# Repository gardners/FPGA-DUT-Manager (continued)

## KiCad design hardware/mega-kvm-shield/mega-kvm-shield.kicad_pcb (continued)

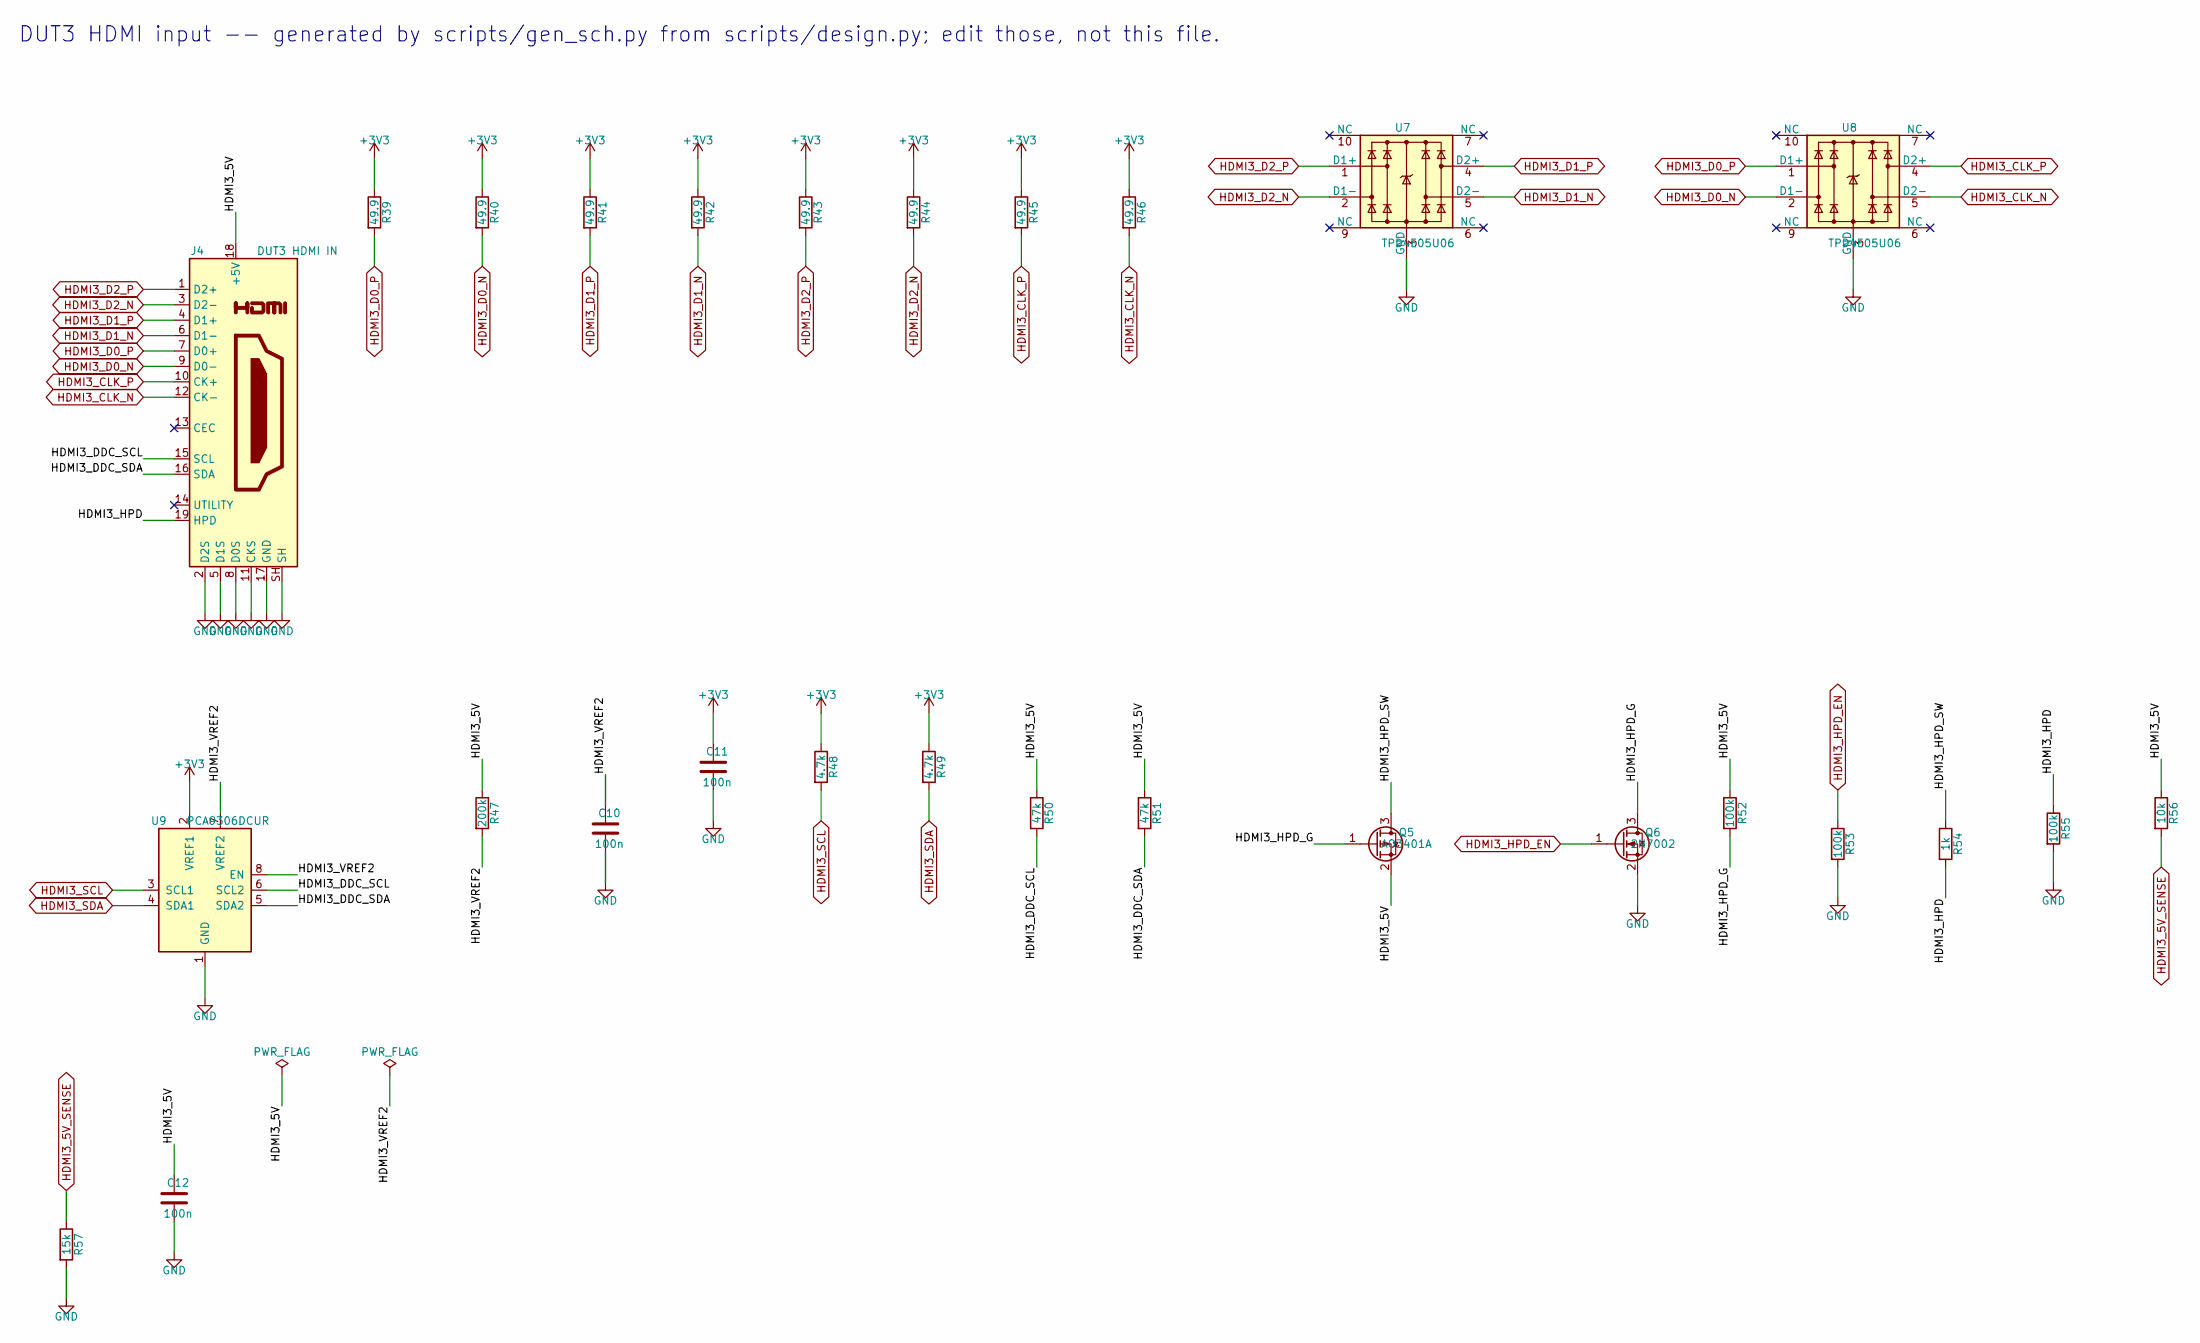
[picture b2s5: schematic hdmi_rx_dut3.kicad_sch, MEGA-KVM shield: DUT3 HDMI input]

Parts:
C10, C11, C12: 100n; C_0402_1005Metric; LCSC C1525
J4: DUT3 HDMI IN; HDMI_A_Amphenol_10029449-x01xLF_Horizontal; MPN Amphenol 10029449-111RLF
Q5: AO3401A; SOT-23; LCSC C15127
Q6: 2N7002; SOT-23; LCSC C8545
R39, R40, R41, R42, R43, R44, R45, R46: 49.9; R_0402_1005Metric; LCSC C25120
R47: 200k; R_0402_1005Metric; LCSC C25811
R48, R49: 4.7k; R_0402_1005Metric; LCSC C25900
R50, R51: 47k; R_0402_1005Metric; LCSC C25792
R52, R53, R55: 100k; R_0402_1005Metric; LCSC C25741
R54: 1k; R_0402_1005Metric; LCSC C11702
R56: 10k; R_0402_1005Metric; LCSC C25744
R57: 15k; R_0402_1005Metric; LCSC C25756
U7, U8: TPD4E05U06; USON-10_2.5x1.0mm_P0.5mm; LCSC C138714
U9: PCA9306DCUR; VSSOP-8_2.3x2mm_P0.5mm

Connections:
+3V3: C11.1, R39.1, R40.1, R41.1, R42.1, R43.1, R44.1, R45.1, R46.1, R48.1, R49.1, U9.2 (VREF1); also elsewhere on the board
GND: C10.2, C11.2, C12.2, J4.2 (D2S), J4.5 (D1S), J4.8 (D0S), J4.11 (CKS), J4.17 (GND), J4.SH, Q6.2 (S), R53.2, R55.2, R57.2, U7.3 (GND), U7.8 (GND), U8.3 (GND), U8.8 (GND), U9.1 (GND); also elsewhere on the board
HDMI3_5V: C12.1, J4.18 (+5V), Q5.2 (S), R47.1, R50.1, R51.1, R52.1, R56.1
HDMI3_5V_SENSE: R56.2, R57.1; also elsewhere on the board
HDMI3_CLK_N: J4.12 (CK-), R46.2, U8.5 (D2-); also elsewhere on the board
HDMI3_CLK_P: J4.10 (CK+), R45.2, U8.4 (D2+); also elsewhere on the board
HDMI3_D0_N: J4.9 (D0-), R40.2, U8.2 (D1-); also elsewhere on the board
HDMI3_D0_P: J4.7 (D0+), R39.2, U8.1 (D1+); also elsewhere on the board
HDMI3_D1_N: J4.6 (D1-), R42.2, U7.5 (D2-); also elsewhere on the board
HDMI3_D1_P: J4.4 (D1+), R41.2, U7.4 (D2+); also elsewhere on the board
HDMI3_D2_N: J4.3 (D2-), R44.2, U7.2 (D1-); also elsewhere on the board
HDMI3_D2_P: J4.1 (D2+), R43.2, U7.1 (D1+); also elsewhere on the board
HDMI3_DDC_SCL: J4.15 (SCL), R50.2, U9.6 (SCL2)
HDMI3_DDC_SDA: J4.16 (SDA), R51.2, U9.5 (SDA2)
HDMI3_HPD: J4.19 (HPD), R54.2, R55.1
HDMI3_HPD_EN: Q6.1 (G), R53.1; also elsewhere on the board
HDMI3_HPD_G: Q5.1 (G), Q6.3 (D), R52.2
HDMI3_HPD_SW: Q5.3 (D), R54.1
HDMI3_SCL: R48.2, U9.3 (SCL1); also elsewhere on the board
HDMI3_SDA: R49.2, U9.4 (SDA1); also elsewhere on the board
HDMI3_VREF2: C10.1, R47.2, U9.7 (VREF2), U9.8 (EN)

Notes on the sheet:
DUT3 HDMI input -- generated by scripts/gen_sch.py from scripts/design.py; edit those, not this file.

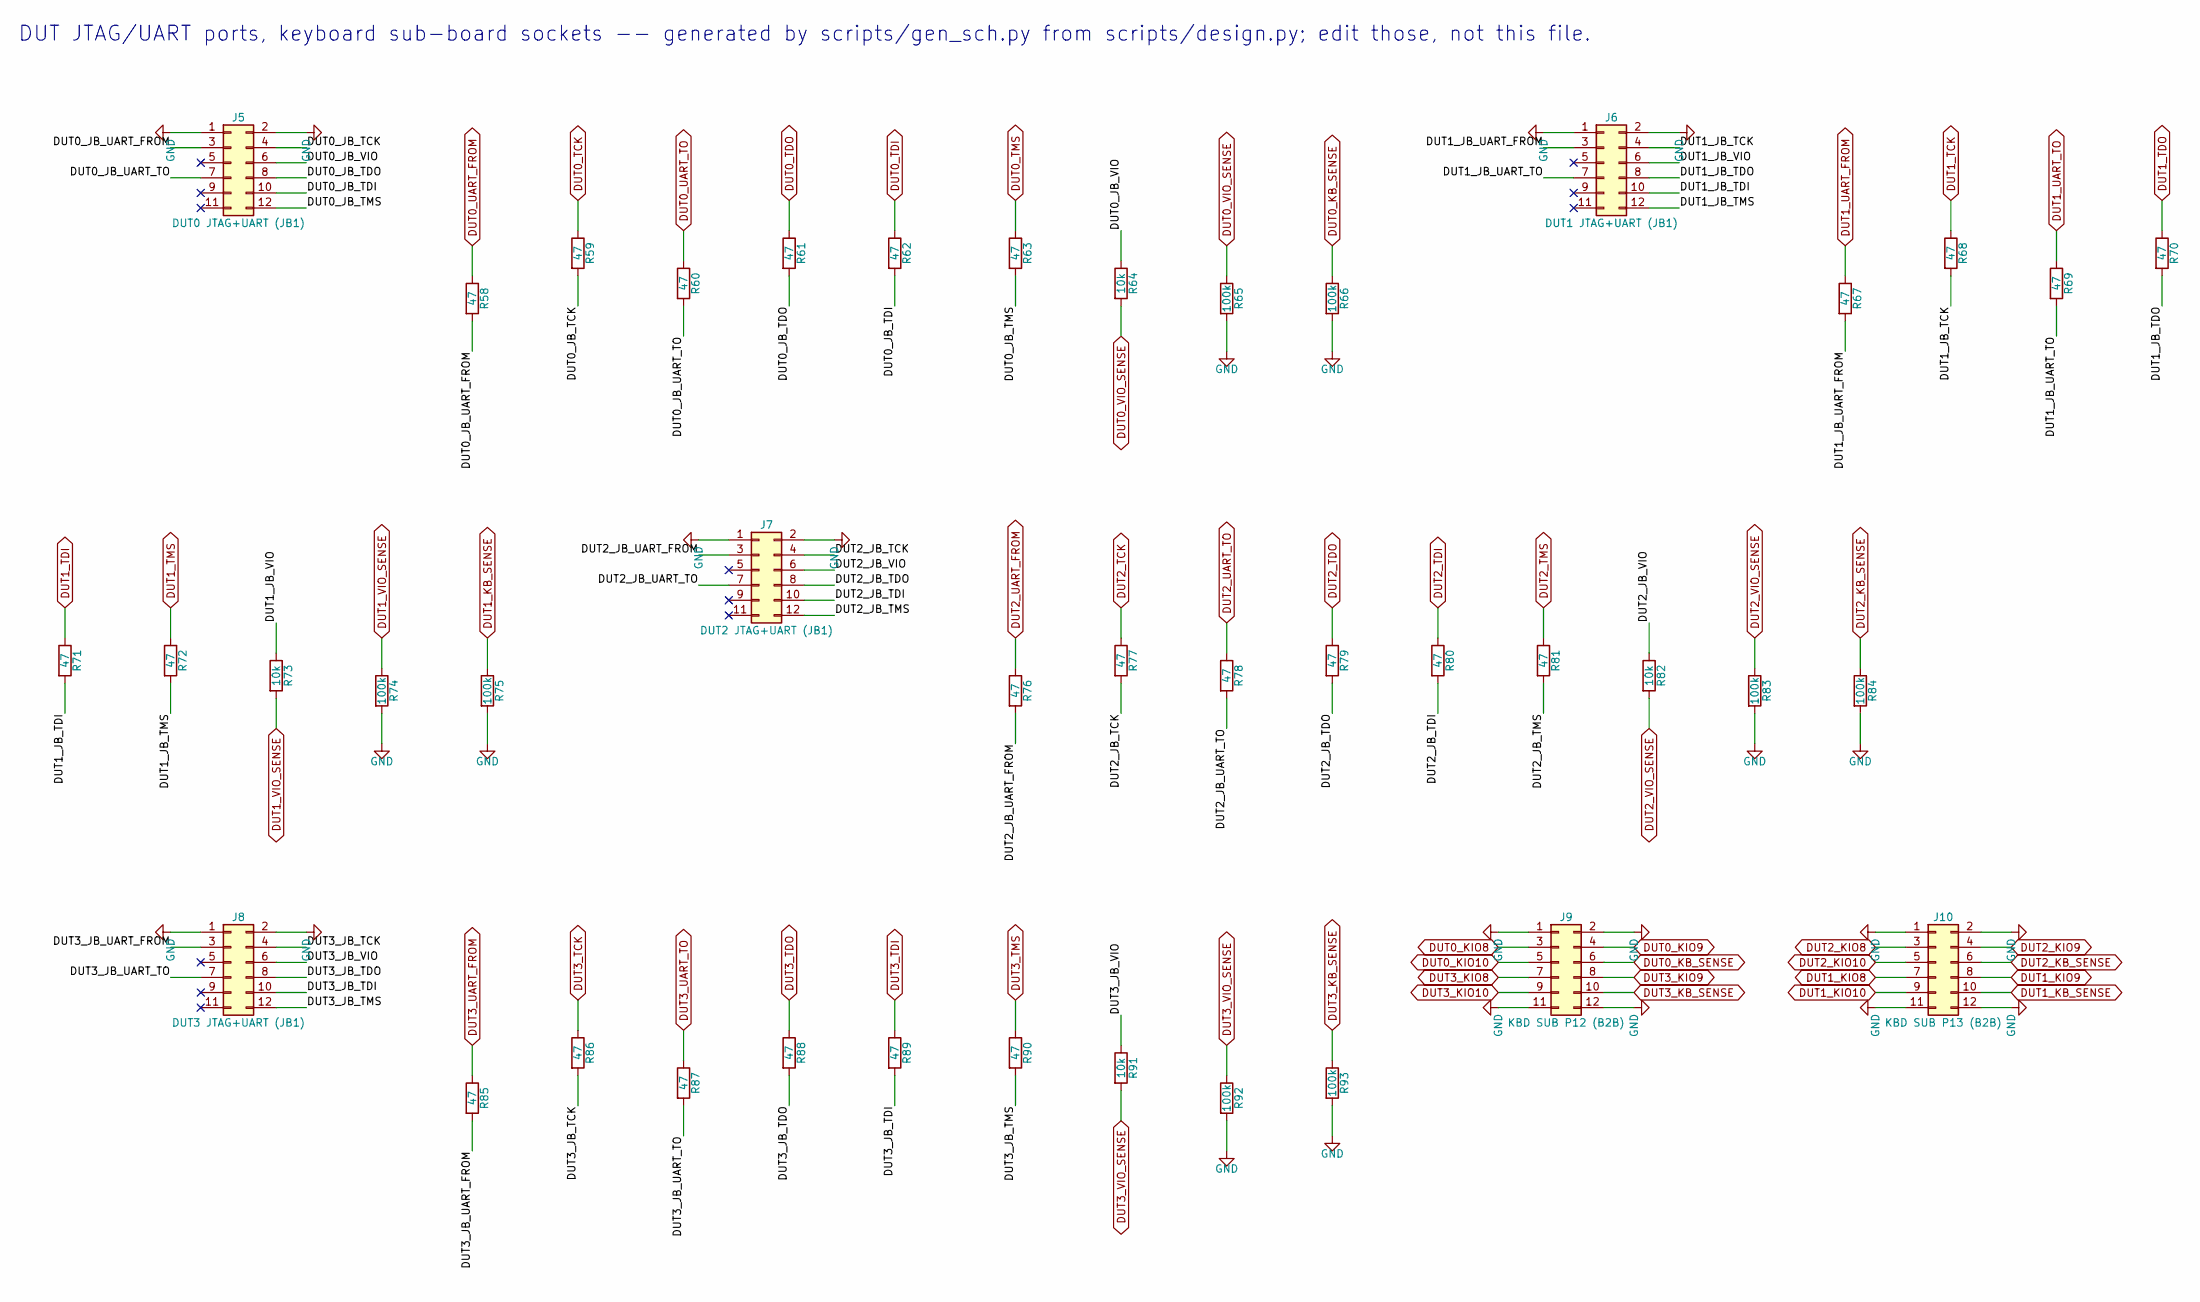
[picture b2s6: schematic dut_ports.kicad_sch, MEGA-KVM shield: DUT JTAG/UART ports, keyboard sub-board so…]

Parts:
J5: DUT0 JTAG+UART (JB1); IDC-Header_2x06_P2.54mm_Horizontal
J6: DUT1 JTAG+UART (JB1); IDC-Header_2x06_P2.54mm_Horizontal
J7: DUT2 JTAG+UART (JB1); IDC-Header_2x06_P2.54mm_Horizontal
J8: DUT3 JTAG+UART (JB1); IDC-Header_2x06_P2.54mm_Horizontal
J9: KBD SUB P12 (B2B); PinSocket_2x06_P2.54mm_Vertical
J10: KBD SUB P13 (B2B); PinSocket_2x06_P2.54mm_Vertical
R58, R59, R60, R61, R62, R63, R67, R68, R69, R70, R71, R72, R76, R77, R78, R79, R80, R81, R85, R86, R87, R88, R89, R90: 47; R_0402_1005Metric; LCSC C25118
R64, R73, R82, R91: 10k; R_0402_1005Metric; LCSC C25744
R65, R66, R74, R75, R83, R84, R92, R93: 100k; R_0402_1005Metric; LCSC C25741

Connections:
DUT0_JB_TCK: J5.4, R59.2
DUT0_JB_TDI: J5.10, R62.2
DUT0_JB_TDO: J5.8, R61.2
DUT0_JB_TMS: J5.12, R63.2
DUT0_JB_UART_FROM: J5.3, R58.2
DUT0_JB_UART_TO: J5.7, R60.2
DUT0_JB_VIO: J5.6, R64.1
DUT0_KB_SENSE: J9.6, R66.1; also elsewhere on the board
DUT0_KIO8: J9.3; also elsewhere on the board
DUT0_KIO9: J9.4; also elsewhere on the board
DUT0_KIO10: J9.5; also elsewhere on the board
DUT0_TCK: R59.1; also elsewhere on the board
DUT0_TDI: R62.1; also elsewhere on the board
DUT0_TDO: R61.1; also elsewhere on the board
DUT0_TMS: R63.1; also elsewhere on the board
DUT0_UART_FROM: R58.1; also elsewhere on the board
DUT0_UART_TO: R60.1; also elsewhere on the board
DUT0_VIO_SENSE: R64.2, R65.1; also elsewhere on the board
DUT1_JB_TCK: J6.4, R68.2
DUT1_JB_TDI: J6.10, R71.2
DUT1_JB_TDO: J6.8, R70.2
DUT1_JB_TMS: J6.12, R72.2
DUT1_JB_UART_FROM: J6.3, R67.2
DUT1_JB_UART_TO: J6.7, R69.2
DUT1_JB_VIO: J6.6, R73.1
DUT1_KB_SENSE: J10.10, R75.1; also elsewhere on the board
DUT1_KIO8: J10.7; also elsewhere on the board
DUT1_KIO9: J10.8; also elsewhere on the board
DUT1_KIO10: J10.9; also elsewhere on the board
DUT1_TCK: R68.1; also elsewhere on the board
DUT1_TDI: R71.1; also elsewhere on the board
DUT1_TDO: R70.1; also elsewhere on the board
DUT1_TMS: R72.1; also elsewhere on the board
DUT1_UART_FROM: R67.1; also elsewhere on the board
DUT1_UART_TO: R69.1; also elsewhere on the board
DUT1_VIO_SENSE: R73.2, R74.1; also elsewhere on the board
DUT2_JB_TCK: J7.4, R77.2
DUT2_JB_TDI: J7.10, R80.2
DUT2_JB_TDO: J7.8, R79.2
DUT2_JB_TMS: J7.12, R81.2
DUT2_JB_UART_FROM: J7.3, R76.2
DUT2_JB_UART_TO: J7.7, R78.2
DUT2_JB_VIO: J7.6, R82.1
DUT2_KB_SENSE: J10.6, R84.1; also elsewhere on the board
DUT2_KIO8: J10.3; also elsewhere on the board
DUT2_KIO9: J10.4; also elsewhere on the board
DUT2_KIO10: J10.5; also elsewhere on the board
DUT2_TCK: R77.1; also elsewhere on the board
DUT2_TDI: R80.1; also elsewhere on the board
DUT2_TDO: R79.1; also elsewhere on the board
DUT2_TMS: R81.1; also elsewhere on the board
DUT2_UART_FROM: R76.1; also elsewhere on the board
DUT2_UART_TO: R78.1; also elsewhere on the board
DUT2_VIO_SENSE: R82.2, R83.1; also elsewhere on the board
DUT3_JB_TCK: J8.4, R86.2
DUT3_JB_TDI: J8.10, R89.2
DUT3_JB_TDO: J8.8, R88.2
DUT3_JB_TMS: J8.12, R90.2
DUT3_JB_UART_FROM: J8.3, R85.2
DUT3_JB_UART_TO: J8.7, R87.2
DUT3_JB_VIO: J8.6, R91.1
DUT3_KB_SENSE: J9.10, R93.1; also elsewhere on the board
DUT3_KIO8: J9.7; also elsewhere on the board
DUT3_KIO9: J9.8; also elsewhere on the board
DUT3_KIO10: J9.9; also elsewhere on the board
DUT3_TCK: R86.1; also elsewhere on the board
DUT3_TDI: R89.1; also elsewhere on the board
DUT3_TDO: R88.1; also elsewhere on the board
DUT3_TMS: R90.1; also elsewhere on the board
DUT3_UART_FROM: R85.1; also elsewhere on the board
DUT3_UART_TO: R87.1; also elsewhere on the board
DUT3_VIO_SENSE: R91.2, R92.1; also elsewhere on the board
GND: J5.1, J5.2, J6.1, J6.2, J7.1, J7.2, J8.1, J8.2, J9.1, J9.2, J9.11, J9.12, J10.1, J10.2, J10.11, J10.12, R65.2, R66.2, R74.2, R75.2, R83.2, R84.2, R92.2, R93.2; also elsewhere on the board

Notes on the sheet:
DUT JTAG/UART ports, keyboard sub-board sockets -- generated by scripts/gen_sch.py from scripts/design.py; edit those, not this file.

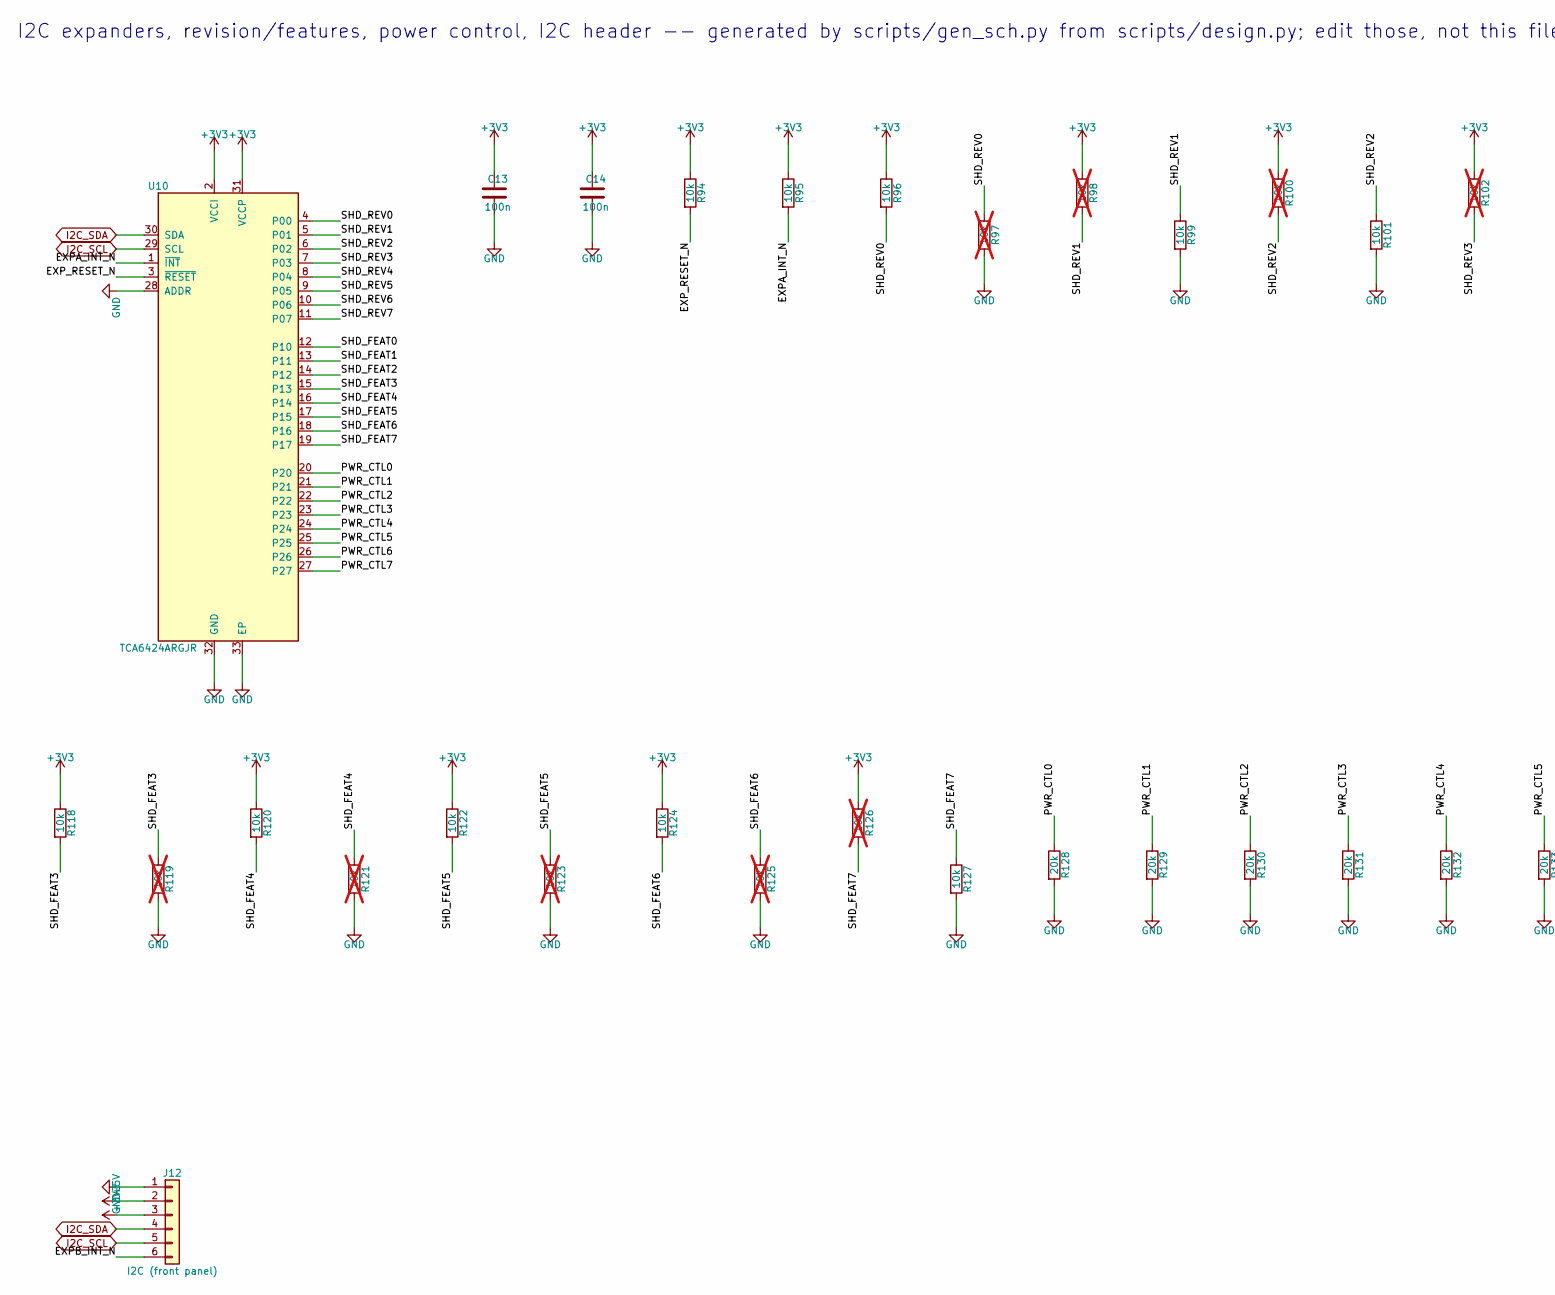
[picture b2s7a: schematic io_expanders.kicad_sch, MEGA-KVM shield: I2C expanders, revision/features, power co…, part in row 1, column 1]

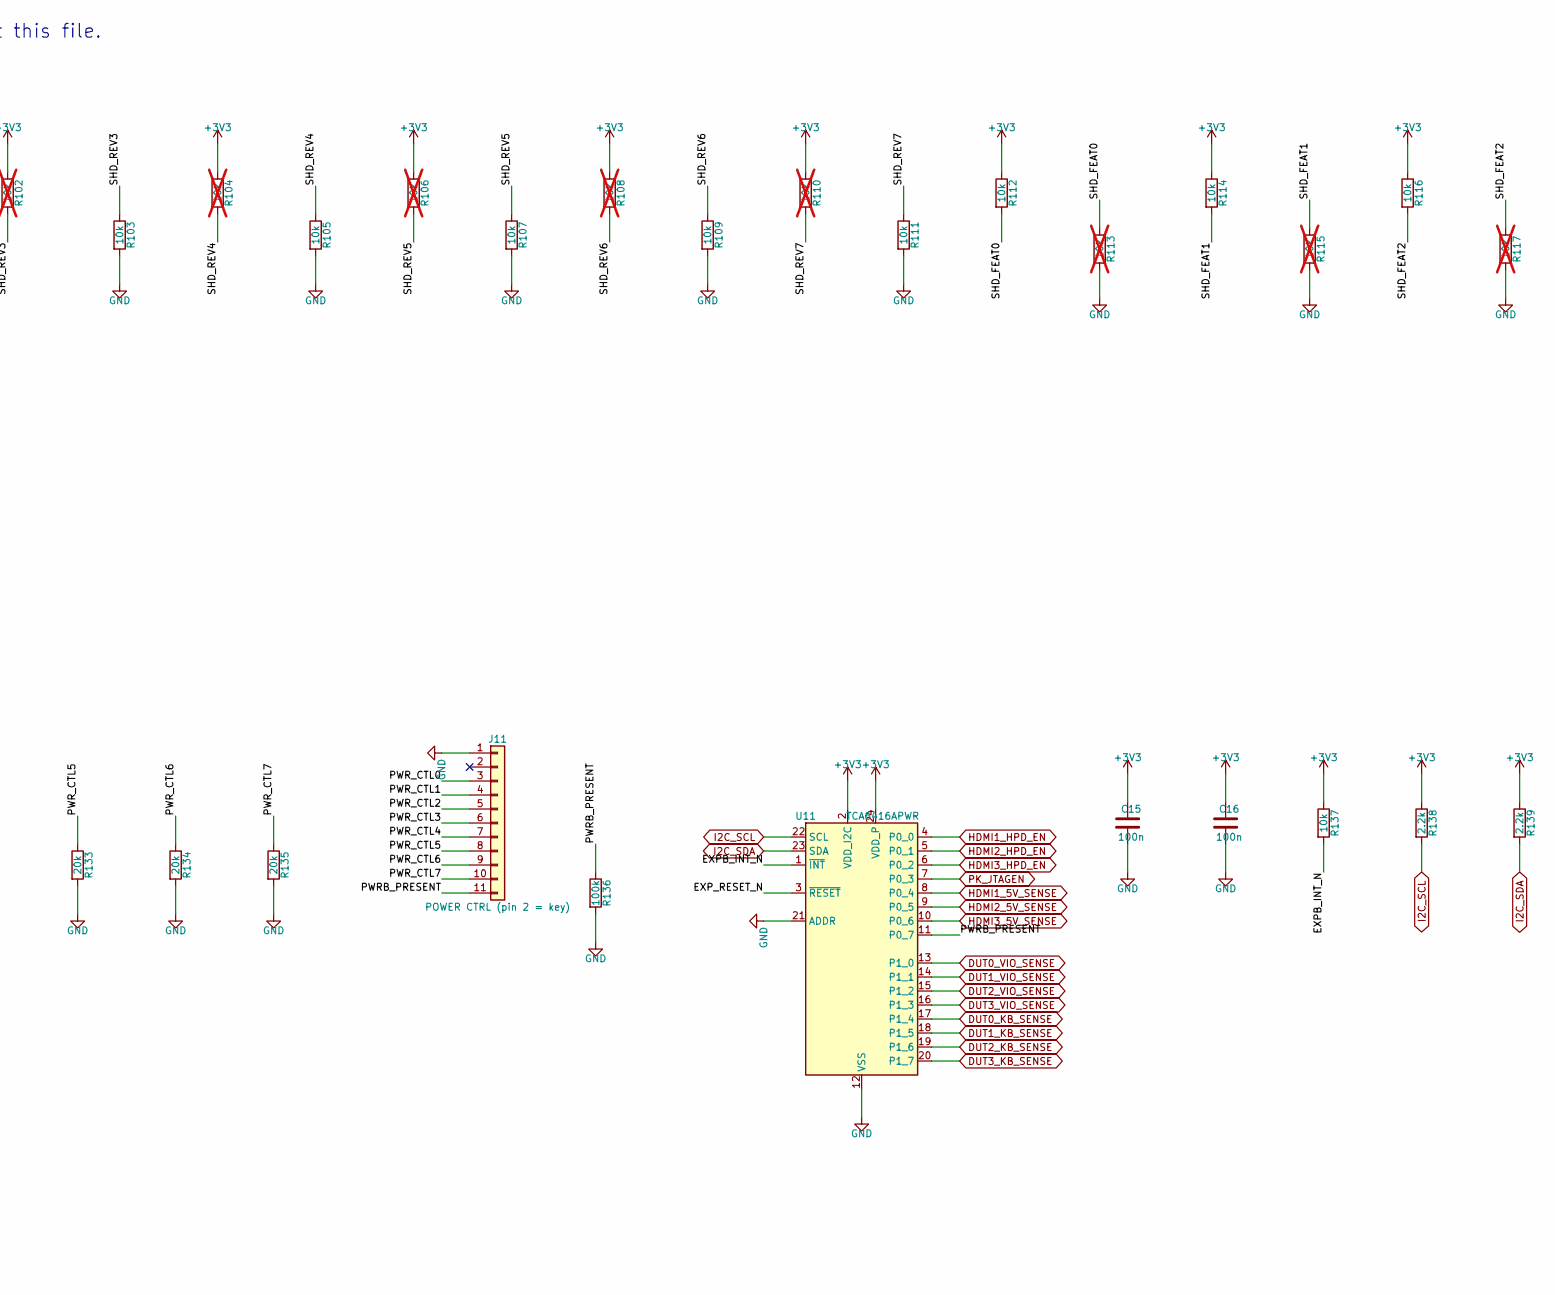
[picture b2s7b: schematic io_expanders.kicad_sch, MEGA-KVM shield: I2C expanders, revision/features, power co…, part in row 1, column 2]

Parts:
C13, C14, C15, C16: 100n; C_0402_1005Metric; LCSC C1525
J11: POWER CTRL (pin 2 = key); PinHeader_1x11_P2.54mm_Vertical
J12: I2C (front panel); PinHeader_1x06_P2.54mm_Horizontal
R94, R95, R96, R99, R101, R103, R105, R107, R109, R111, R112, R114, R116, R118, R120, R122, R124, R127, R137: 10k; R_0402_1005Metric; LCSC C25744
R97, R98, R100, R102, R104, R106, R108, R110, R113, R115, R117, R119, R121, R123, R125, R126: 10k; R_0402_1005Metric; LCSC C25744; not fitted
R128, R129, R130, R131, R132, R133, R134, R135: 20k; R_0402_1005Metric; LCSC C25765
R136: 100k; R_0402_1005Metric; LCSC C25741
R138, R139: 2.2k; R_0402_1005Metric; LCSC C25879
U10: TCA6424ARGJR; QFN-32-1EP_5x5mm_P0.5mm_EP3.45x3.45mm
U11: TCA6416APWR; TSSOP-24_4.4x7.8mm_P0.65mm

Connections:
+3V3: C13.1, C14.1, C15.1, C16.1, J12.3, R94.1, R95.1, R96.1, R98.1, R100.1, R102.1, R104.1, R106.1, R108.1, R110.1, R112.1, R114.1, R116.1, R118.1, R120.1, R122.1, R124.1, R126.1, R137.1, R138.1, R139.1, U10.2 (VCCI), U10.31 (VCCP), U11.2 (VDD_I2C), U11.24 (VDD_P); also elsewhere on the board
+5V: J12.2; also elsewhere on the board
DUT0_KB_SENSE: U11.17 (P1_4); also elsewhere on the board
DUT0_VIO_SENSE: U11.13 (P1_0); also elsewhere on the board
DUT1_KB_SENSE: U11.18 (P1_5); also elsewhere on the board
DUT1_VIO_SENSE: U11.14 (P1_1); also elsewhere on the board
DUT2_KB_SENSE: U11.19 (P1_6); also elsewhere on the board
DUT2_VIO_SENSE: U11.15 (P1_2); also elsewhere on the board
DUT3_KB_SENSE: U11.20 (P1_7); also elsewhere on the board
DUT3_VIO_SENSE: U11.16 (P1_3); also elsewhere on the board
EXPA_INT_N: R95.2, U10.1 (~INT)
EXPB_INT_N: J12.6, R137.2, U11.1 (~INT)
EXP_RESET_N: R94.2, U10.3 (~RESET), U11.3 (~RESET)
GND: C13.2, C14.2, C15.2, C16.2, J11.1, J12.1, R97.2, R99.2, R101.2, R103.2, R105.2, R107.2, R109.2, R111.2, R113.2, R115.2, R117.2, R119.2, R121.2, R123.2, R125.2, R127.2, R128.2, R129.2, R130.2, R131.2, R132.2, R133.2, R134.2, R135.2, R136.2, U10.28 (ADDR), U10.32 (GND), U10.33 (EP), U11.12 (VSS), U11.21 (ADDR); also elsewhere on the board
HDMI1_5V_SENSE: U11.8 (P0_4); also elsewhere on the board
HDMI1_HPD_EN: U11.4 (P0_0); also elsewhere on the board
HDMI2_5V_SENSE: U11.9 (P0_5); also elsewhere on the board
HDMI2_HPD_EN: U11.5 (P0_1); also elsewhere on the board
HDMI3_5V_SENSE: U11.10 (P0_6); also elsewhere on the board
HDMI3_HPD_EN: U11.6 (P0_2); also elsewhere on the board
I2C_SCL: J12.5, R138.2, U10.29 (SCL), U11.22 (SCL); also elsewhere on the board
I2C_SDA: J12.4, R139.2, U10.30 (SDA), U11.23 (SDA); also elsewhere on the board
PK_JTAGEN: U11.7 (P0_3); also elsewhere on the board
PWRB_PRESENT: J11.11, R136.1, U11.11 (P0_7)
PWR_CTL0: J11.3, R128.1, U10.20
PWR_CTL1: J11.4, R129.1, U10.21
PWR_CTL2: J11.5, R130.1, U10.22
PWR_CTL3: J11.6, R131.1, U10.23
PWR_CTL4: J11.7, R132.1, U10.24
PWR_CTL5: J11.8, R133.1, U10.25
PWR_CTL6: J11.9, R134.1, U10.26
PWR_CTL7: J11.10, R135.1, U10.27
SHD_FEAT0: R112.2, R113.1, U10.12 (P10)
SHD_FEAT1: R114.2, R115.1, U10.13 (P11)
SHD_FEAT2: R116.2, R117.1, U10.14 (P12)
SHD_FEAT3: R118.2, R119.1, U10.15 (P13)
SHD_FEAT4: R120.2, R121.1, U10.16 (P14)
SHD_FEAT5: R122.2, R123.1, U10.17 (P15)
SHD_FEAT6: R124.2, R125.1, U10.18 (P16)
SHD_FEAT7: R126.2, R127.1, U10.19 (P17)
SHD_REV0: R96.2, R97.1, U10.4 (P00)
SHD_REV1: R98.2, R99.1, U10.5 (P01)
SHD_REV2: R100.2, R101.1, U10.6 (P02)
SHD_REV3: R102.2, R103.1, U10.7 (P03)
SHD_REV4: R104.2, R105.1, U10.8 (P04)
SHD_REV5: R106.2, R107.1, U10.9 (P05)
SHD_REV6: R108.2, R109.1, U10.10 (P06)
SHD_REV7: R110.2, R111.1, U10.11 (P07)

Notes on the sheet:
I2C expanders, revision/features, power control, I2C header -- generated by scripts/gen_sch.py from scripts/design.py; edit those, not this file.

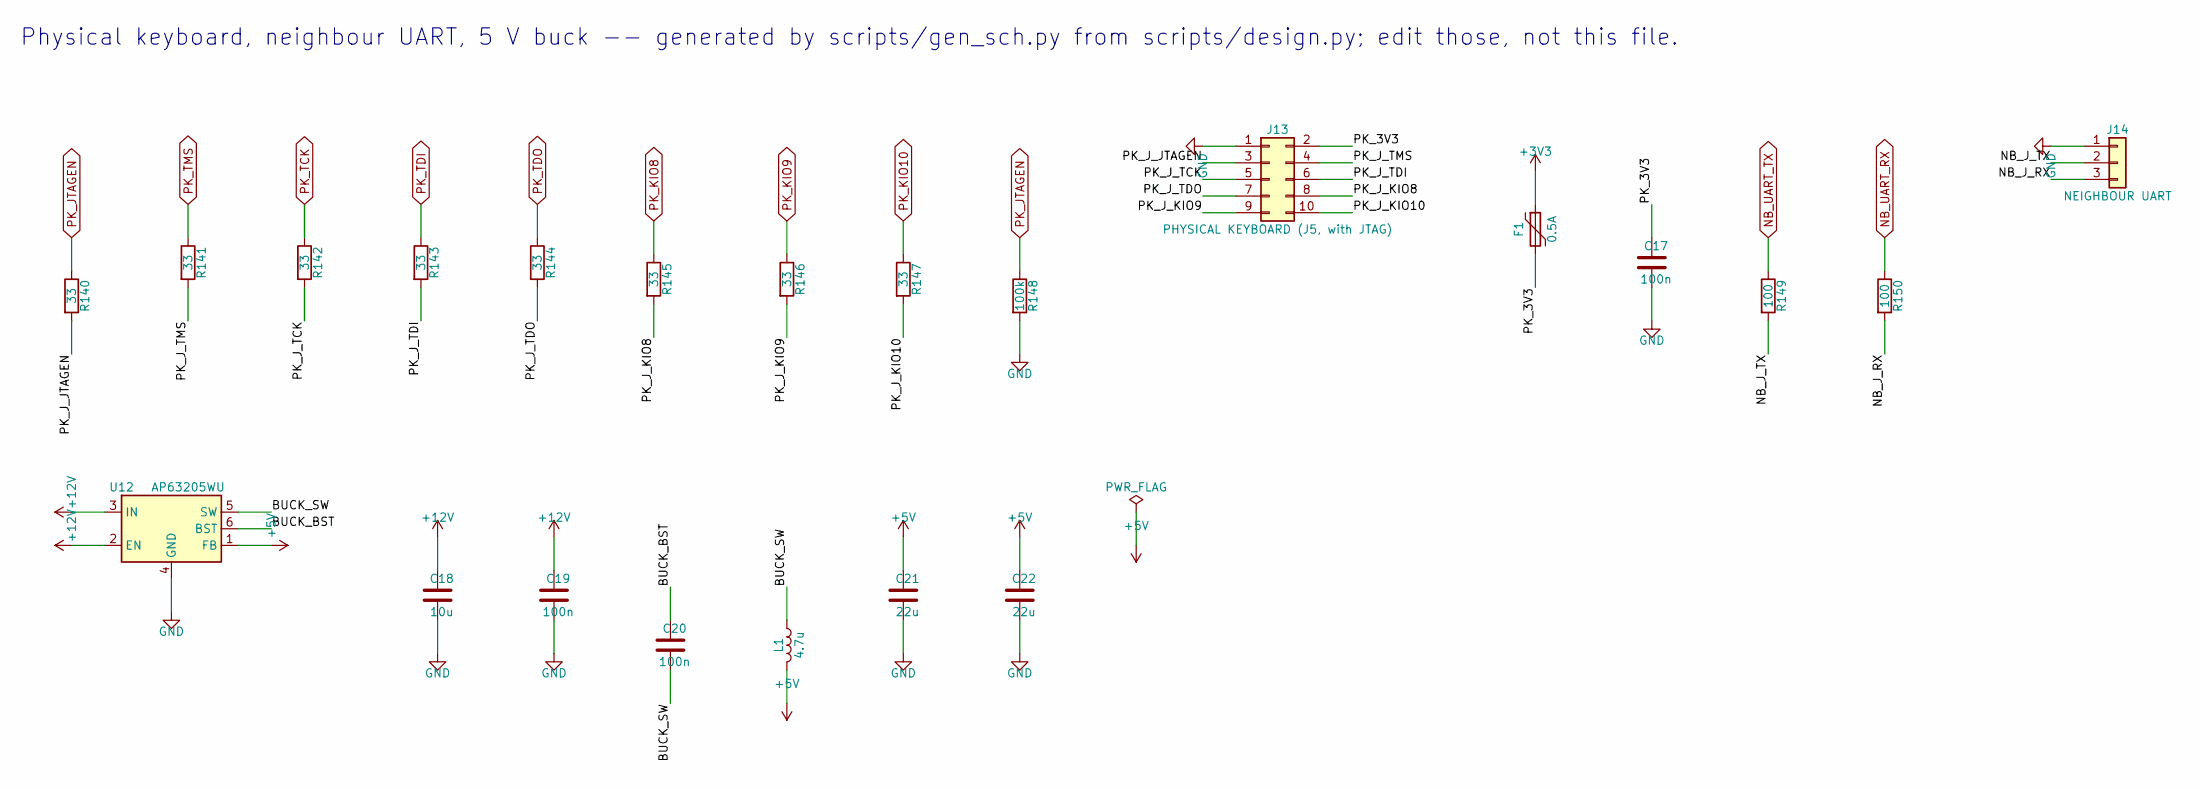
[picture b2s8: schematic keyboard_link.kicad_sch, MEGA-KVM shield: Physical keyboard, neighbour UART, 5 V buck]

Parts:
C17, C19, C20: 100n; C_0402_1005Metric; LCSC C1525
C18: 10u; C_1206_3216Metric
C21, C22: 22u; C_0805_2012Metric
F1: 0.5A; Fuse_1206_3216Metric
J13: PHYSICAL KEYBOARD (J5, with JTAG); IDC-Header_2x05_P2.54mm_Horizontal
J14: NEIGHBOUR UART; PinHeader_1x03_P2.54mm_Vertical
L1: 4.7u; L_Changjiang_FXL0530
R140, R141, R142, R143, R144, R145, R146, R147: 33; R_0402_1005Metric; LCSC C25105
R148: 100k; R_0402_1005Metric; LCSC C25741
R149, R150: 100; R_0402_1005Metric; LCSC C25076
U12: AP63205WU; TSOT-23-6

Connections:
+3V3: F1.1; also elsewhere on the board
+5V: C21.1, C22.1, L1.2, U12.1 (FB); also elsewhere on the board
+12V: C18.1, C19.1, U12.2 (EN), U12.3 (IN); also elsewhere on the board
BUCK_BST: C20.1, U12.6 (BST)
BUCK_SW: C20.2, L1.1, U12.5 (SW)
GND: C17.2, C18.2, C19.2, C21.2, C22.2, J13.1, J14.1, R148.2, U12.4 (GND); also elsewhere on the board
NB_J_RX: J14.3, R150.2
NB_J_TX: J14.2, R149.2
NB_UART_RX: R150.1; also elsewhere on the board
NB_UART_TX: R149.1; also elsewhere on the board
PK_3V3: C17.1, F1.2, J13.2
PK_JTAGEN: R140.1, R148.1; also elsewhere on the board
PK_J_JTAGEN: J13.3, R140.2
PK_J_KIO8: J13.8, R145.2
PK_J_KIO9: J13.9, R146.2
PK_J_KIO10: J13.10, R147.2
PK_J_TCK: J13.5, R142.2
PK_J_TDI: J13.6, R143.2
PK_J_TDO: J13.7, R144.2
PK_J_TMS: J13.4, R141.2
PK_KIO8: R145.1; also elsewhere on the board
PK_KIO9: R146.1; also elsewhere on the board
PK_KIO10: R147.1; also elsewhere on the board
PK_TCK: R142.1; also elsewhere on the board
PK_TDI: R143.1; also elsewhere on the board
PK_TDO: R144.1; also elsewhere on the board
PK_TMS: R141.1; also elsewhere on the board

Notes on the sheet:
Physical keyboard, neighbour UART, 5 V buck -- generated by scripts/gen_sch.py from scripts/design.py; edit those, not this file.

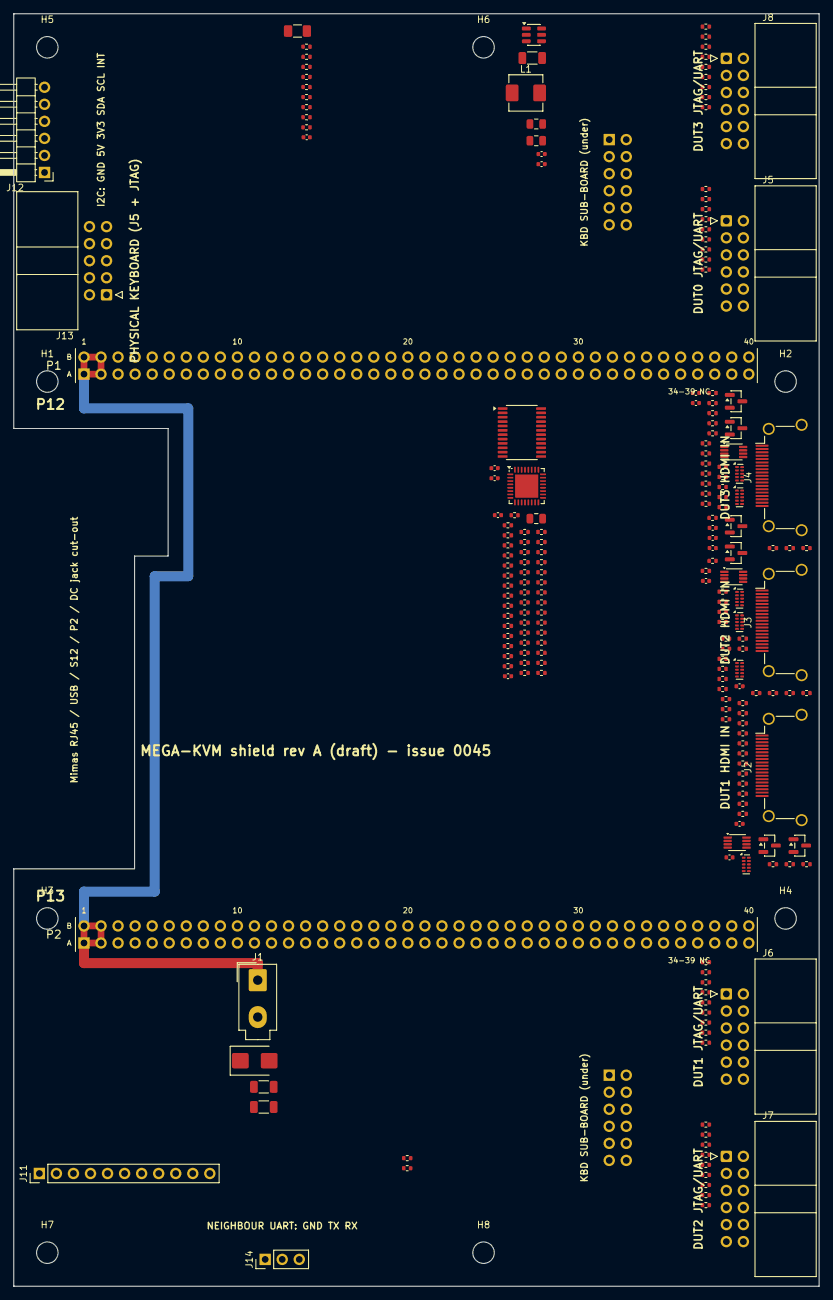
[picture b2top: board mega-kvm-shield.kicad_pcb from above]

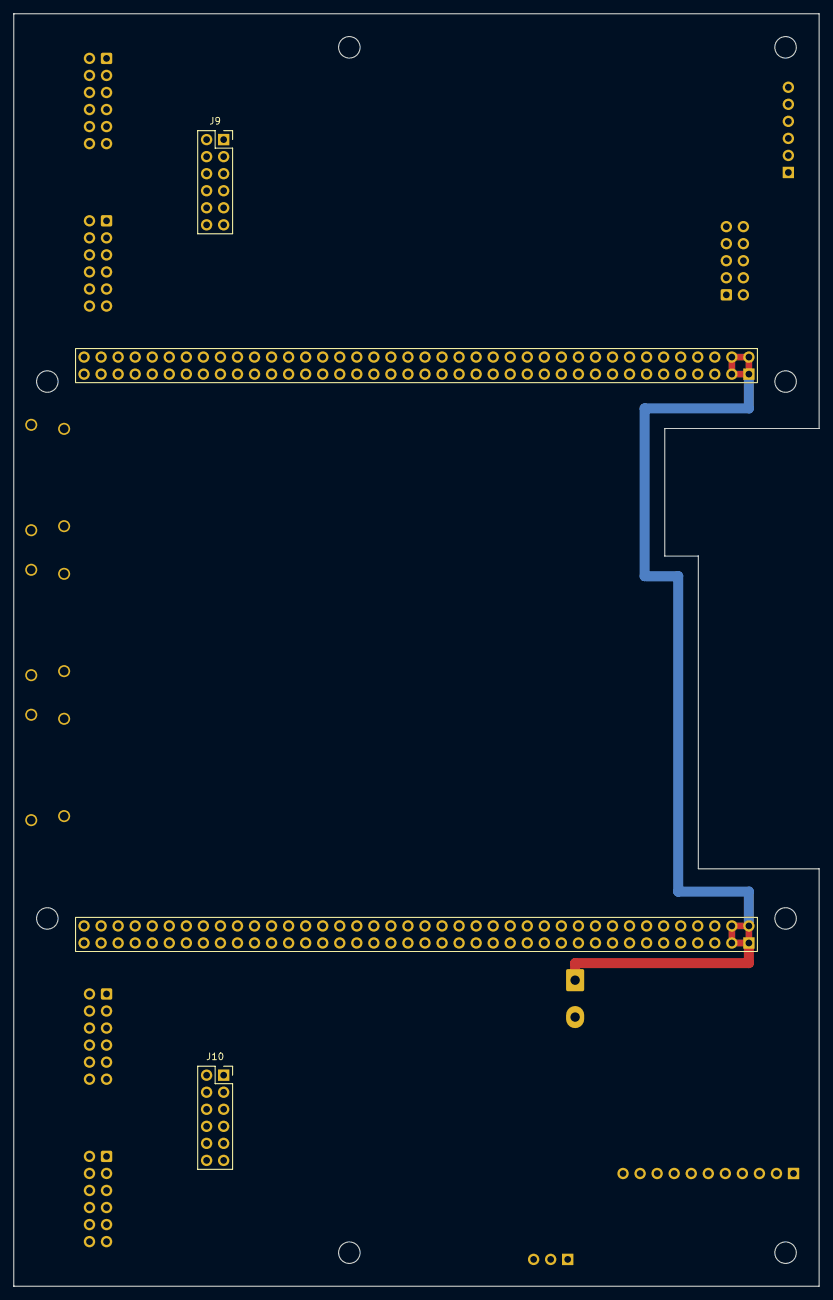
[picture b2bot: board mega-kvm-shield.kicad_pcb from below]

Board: 4 copper layers, 120.0 x 189.6 mm, 217 parts (2 on the bottom side), 186 nets.

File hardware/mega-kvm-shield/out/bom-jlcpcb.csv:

Comment,Designator,Footprint,LCSC Part #,MPN,Qty
10u,"C1,C2,C18",C_1206_3216Metric,TBD,,3
22u,"C21,C22",C_0805_2012Metric,TBD,,2
10u,C3,C_0805_2012Metric,C15850,,1
100n,"C4,C5,C6,C7,C8,C9,C10,C11,C12,C13,C14,C15,C16,C17,C19,C20",C_0402_1005Metric,C1525,,16
SMBJ15A,D1,D_SMB,TBD,,1
0.5A,F1,Fuse_1206_3216Metric,TBD,,1
12V IN,J1,Molex_Mini-Fit_Jr_5566-02A_2x01_P4.20mm_Vertical,TBD,Molex 5566-02A (39-30-1020 class),1
KBD SUB P13 (B2B),J10,PinSocket_2x06_P2.54mm_Vertical,TBD,,1
POWER CTRL (pin 2 = key),J11,PinHeader_1x11_P2.54mm_Vertical,TBD,,1
I2C (front panel),J12,PinHeader_1x06_P2.54mm_Horizontal,TBD,,1
"PHYSICAL KEYBOARD (J5, with JTAG)",J13,IDC-Header_2x05_P2.54mm_Horizontal,TBD,,1
NEIGHBOUR UART,J14,PinHeader_1x03_P2.54mm_Vertical,TBD,,1
DUT1 HDMI IN,J2,HDMI_A_Amphenol_10029449-x01xLF_Horizontal,TBD,Amphenol 10029449-111RLF,1
DUT2 HDMI IN,J3,HDMI_A_Amphenol_10029449-x01xLF_Horizontal,TBD,Amphenol 10029449-111RLF,1
DUT3 HDMI IN,J4,HDMI_A_Amphenol_10029449-x01xLF_Horizontal,TBD,Amphenol 10029449-111RLF,1
DUT0 JTAG+UART (JB1),J5,IDC-Header_2x06_P2.54mm_Horizontal,TBD,,1
DUT1 JTAG+UART (JB1),J6,IDC-Header_2x06_P2.54mm_Horizontal,TBD,,1
DUT2 JTAG+UART (JB1),J7,IDC-Header_2x06_P2.54mm_Horizontal,TBD,,1
DUT3 JTAG+UART (JB1),J8,IDC-Header_2x06_P2.54mm_Horizontal,TBD,,1
KBD SUB P12 (B2B),J9,PinSocket_2x06_P2.54mm_Vertical,TBD,,1
4.7u,L1,L_Changjiang_FXL0530,TBD,,1
P12 socket (DUT0/DUT3 side),P1,Mimas_Header_Socket_2x40,TBD,,1
P13 socket (DUT1/DUT2 side),P2,Mimas_Header_Socket_2x40,TBD,,1
AO3401A,"Q1,Q3,Q5",SOT-23,C15127,,3
2N7002,"Q2,Q4,Q6",SOT-23,C8545,,3
49.9,"R1,R2,R3,R4,R5,R6,R7,R8,R20,R21,R22,R23,R24,R25,R26,R27,R39,R40,R41,R42,R43,R44,R45,R46",R_0402_1005Metric,C25120,,24
4.7k,"R10,R11,R29,R30,R48,R49",R_0402_1005Metric,C25900,,6
47k,"R12,R13,R31,R32,R50,R51",R_0402_1005Metric,C25792,,6
20k,"R128,R129,R130,R131,R132,R133,R134,R135",R_0402_1005Metric,C25765,,8
2.2k,"R138,R139",R_0402_1005Metric,C25879,,2
100k,"R14,R15,R17,R33,R34,R36,R52,R53,R55,R65,R66,R74,R75,R83,R84,R92,R93,R136,R148",R_0402_1005Metric,C25741,,19
33,"R140,R141,R142,R143,R144,R145,R146,R147",R_0402_1005Metric,C25105,,8
100,"R149,R150",R_0402_1005Metric,C25076,,2
1k,"R16,R35,R54",R_0402_1005Metric,C11702,,3
10k,"R18,R37,R56,R64,R73,R82,R91,R94,R95,R96,R99,R101,R103,R105,R107,R109,R111,R112,R114,R116,R118,R120,R122,R124,R127,R137",R_0402_1005Metric,C25744,,26
15k,"R19,R38,R57",R_0402_1005Metric,C25756,,3
47,"R58,R59,R60,R61,R62,R63,R67,R68,R69,R70,R71,R72,R76,R77,R78,R79,R80,R81,R85,R86,R87,R88,R89,R90",R_0402_1005Metric,C25118,,24
200k,"R9,R28,R47",R_0402_1005Metric,C25811,,3
TPD4E05U06,"U1,U2,U4,U5,U7,U8",USON-10_2.5x1.0mm_P0.5mm,C138714,,6
TCA6424ARGJR,U10,QFN-32-1EP_5x5mm_P0.5mm_EP3.45x3.45mm,TBD,,1
TCA6416APWR,U11,TSSOP-24_4.4x7.8mm_P0.65mm,TBD,,1
AP63205WU,U12,TSOT-23-6,TBD,,1
PCA9306DCUR,"U3,U6,U9",VSSOP-8_2.3x2mm_P0.5mm,TBD,,3
